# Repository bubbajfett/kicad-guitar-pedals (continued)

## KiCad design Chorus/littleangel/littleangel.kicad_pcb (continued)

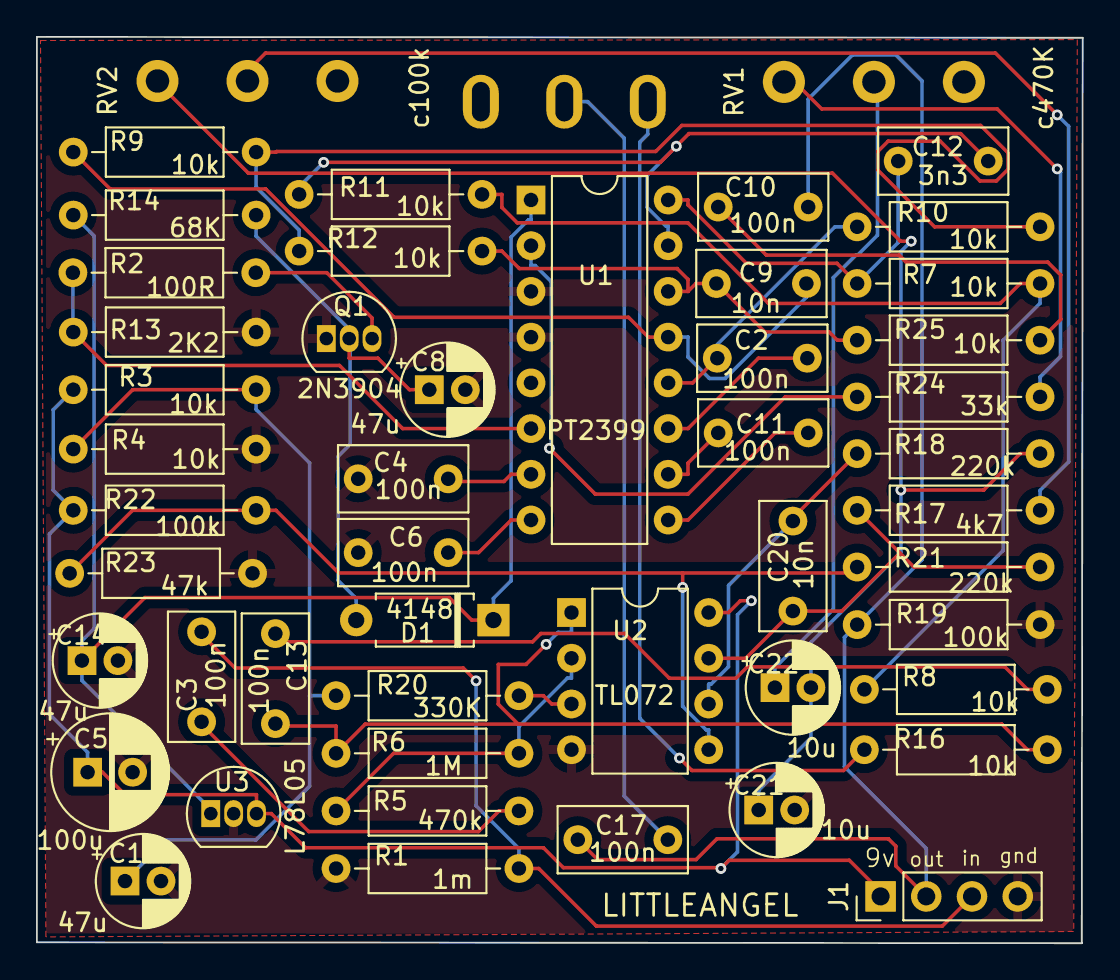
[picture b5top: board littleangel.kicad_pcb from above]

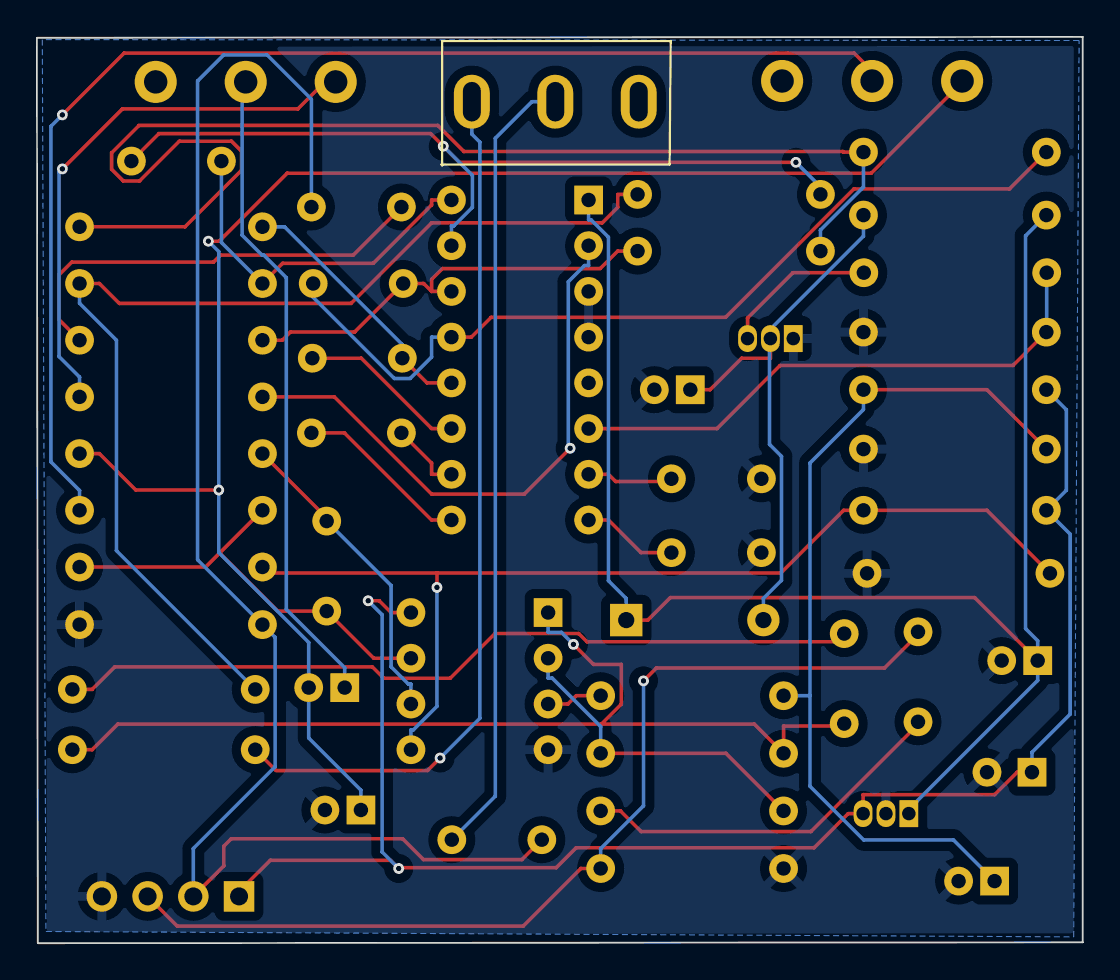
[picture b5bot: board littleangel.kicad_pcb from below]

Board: 2 copper layers, 58.1 x 50.3 mm, 50 parts (3 on the bottom side), 37 nets.

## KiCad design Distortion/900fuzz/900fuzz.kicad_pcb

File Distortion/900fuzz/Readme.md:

# 900 Fuzz

This is a clone of the 900 Fuzz by Fairfield Circuitry.

The first build had a "non-connected" base of Q4. I missed it, and
none of the kicad rules-checker caught it, or I ignored it.   Anyway,
the 2nd try I was more careful not to ignore any ERC errors.

This was based on the Pedalpcb NeinFuzz schematic, which does not specify the JFET.    Dirtboxlayouts shows J201

All trademarks belong to their respective owners.

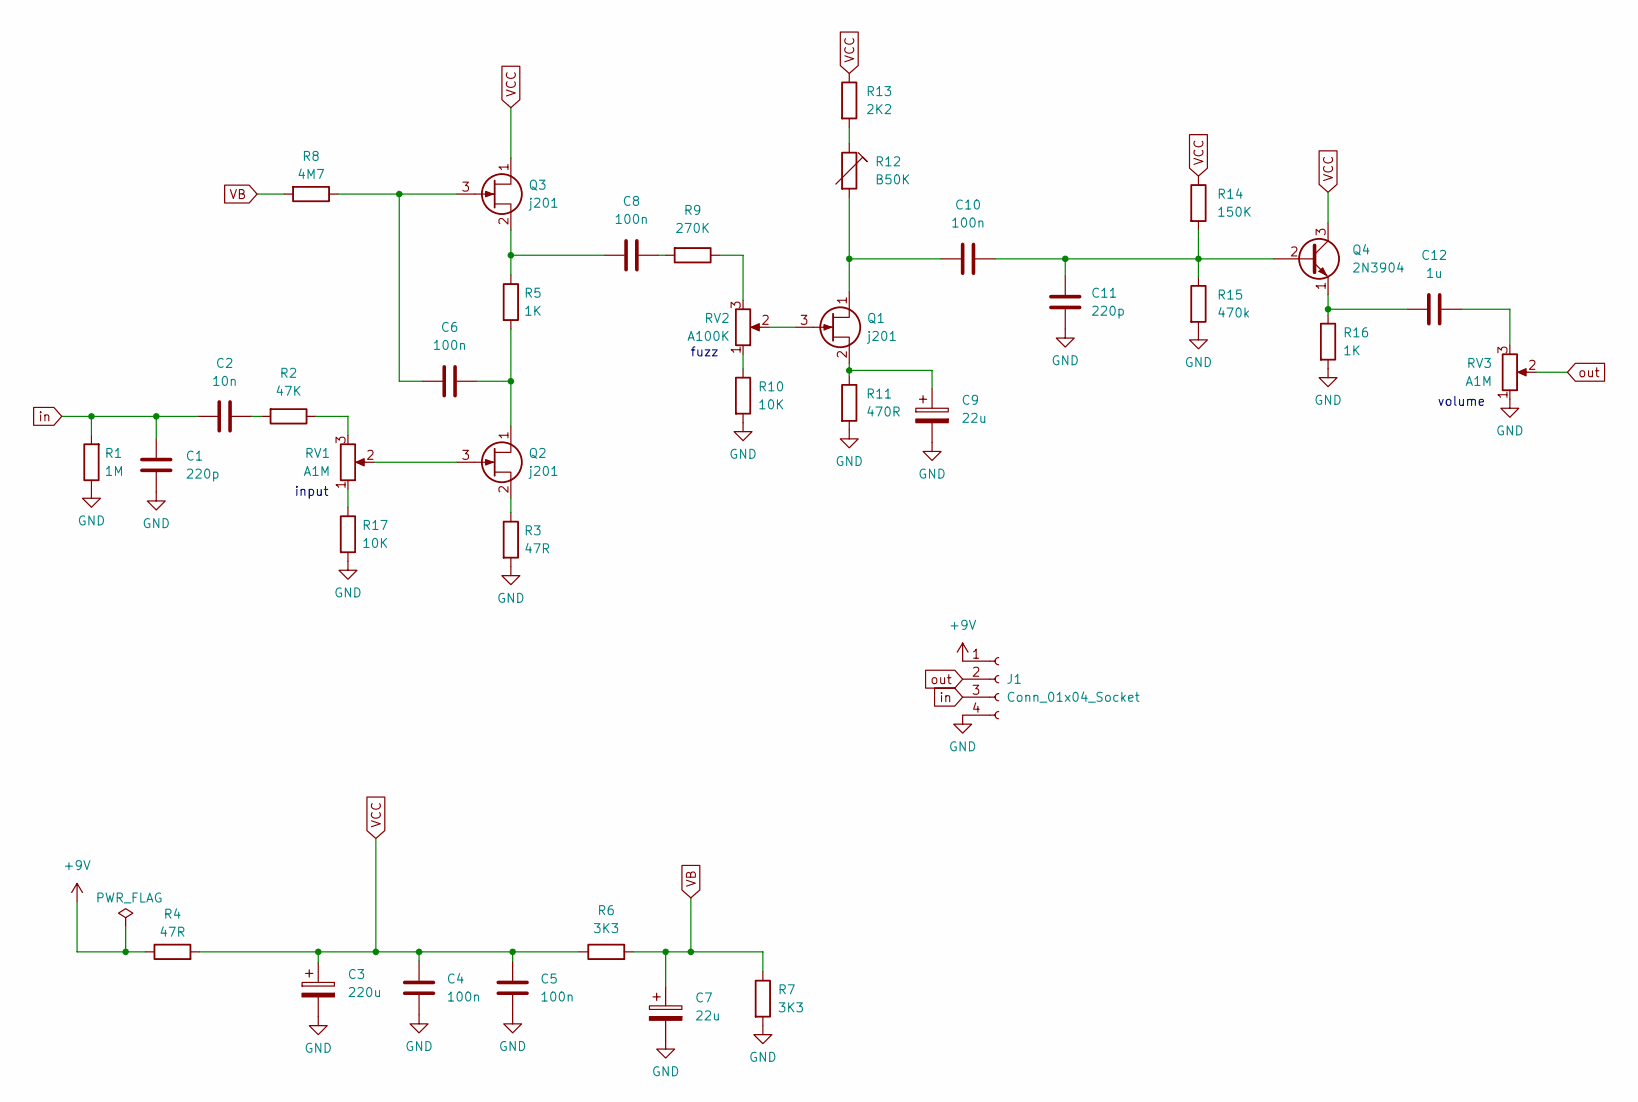
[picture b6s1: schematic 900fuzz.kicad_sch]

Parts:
C1, C11: 220p; C_Disc_D5.0mm_W2.5mm_P2.50mm
C2: 10n; C_Rect_L7.0mm_W2.5mm_P5.00mm
C3: 220u; CP_Radial_D6.3mm_P2.50mm
C4, C5, C6, C8, C10: 100n; C_Rect_L7.0mm_W2.5mm_P5.00mm
C7, C9: 22u; CP_Radial_D5.0mm_P2.00mm
C12: 1u; C_Rect_L7.0mm_W2.5mm_P5.00mm
J1: Conn_01x04_Socket; PinHeader_1x04_P2.54mm_Vertical
Q1, Q2, Q3: j201; TO92-SMD
Q4: 2N3904; TO-92_Inline_Wide
R1: 1M; R_Axial_DIN0207_L6.3mm_D2.5mm_P10.16mm_Horizontal
R2: 47K; R_Axial_DIN0207_L6.3mm_D2.5mm_P10.16mm_Horizontal
R3, R4: 47R; R_Axial_DIN0207_L6.3mm_D2.5mm_P10.16mm_Horizontal
R5, R16: 1K; R_Axial_DIN0207_L6.3mm_D2.5mm_P10.16mm_Horizontal
R6, R7: 3K3; R_Axial_DIN0207_L6.3mm_D2.5mm_P10.16mm_Horizontal
R8: 4M7; R_Axial_DIN0207_L6.3mm_D2.5mm_P10.16mm_Horizontal
R9: 270K; R_Axial_DIN0207_L6.3mm_D2.5mm_P10.16mm_Horizontal
R10, R17: 10K; R_Axial_DIN0207_L6.3mm_D2.5mm_P10.16mm_Horizontal
R11: 470R; R_Axial_DIN0207_L6.3mm_D2.5mm_P10.16mm_Horizontal
R12: B50K; Potentiometer_Runtron_RM-065_Vertical
R13: 2K2; R_Axial_DIN0207_L6.3mm_D2.5mm_P10.16mm_Horizontal
R14: 150K; R_Axial_DIN0207_L6.3mm_D2.5mm_P10.16mm_Horizontal
R15: 470k; R_Axial_DIN0207_L6.3mm_D2.5mm_P10.16mm_Horizontal
RV1, RV3: A1M; Pot_Underside
RV2: A100K; Pot_Underside

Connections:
+9V: J1.1, R4.1
GND: C1.2, C3.2, C4.1, C5.1, C7.2, C9.2, C11.1, J1.4, R1.1, R3.2, R7.2, R10.2, R11.2, R15.2, R16.2, R17.2, RV3.1
unnamed: C2.2, R2.2
unnamed: C8.2, R9.2
unnamed: C12.2, RV3.3
unnamed: C10.1, Q1.1 (D), R12.2
unnamed: Q1.3 (G), RV2.2
unnamed: C9.1, Q1.2 (S), R11.1
unnamed: C6.2, Q2.1 (D), R5.2
unnamed: Q2.3 (G), RV1.2
unnamed: Q2.2 (S), R3.1
unnamed: C6.1, Q3.3 (G), R8.1
unnamed: C8.1, Q3.2 (S), R5.1
unnamed: C10.2, C11.2, Q4.2 (B), R14.2, R15.1
unnamed: C12.1, Q4.1 (E), R16.1
unnamed: R2.1, RV1.3
unnamed: R9.1, RV2.3
unnamed: R10.1, RV2.1
unnamed: R12.1, R13.2
unnamed: R17.1, RV1.1
VB: C7.1, R6.2, R7.1, R8.2
VCC: C3.1, C4.2, C5.2, Q3.1 (D), Q4.3 (C), R4.2, R6.1, R13.1, R14.1
in: C1.1, C2.1, J1.3, R1.2
out: J1.2, RV3.2

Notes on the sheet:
volume
fuzz
input

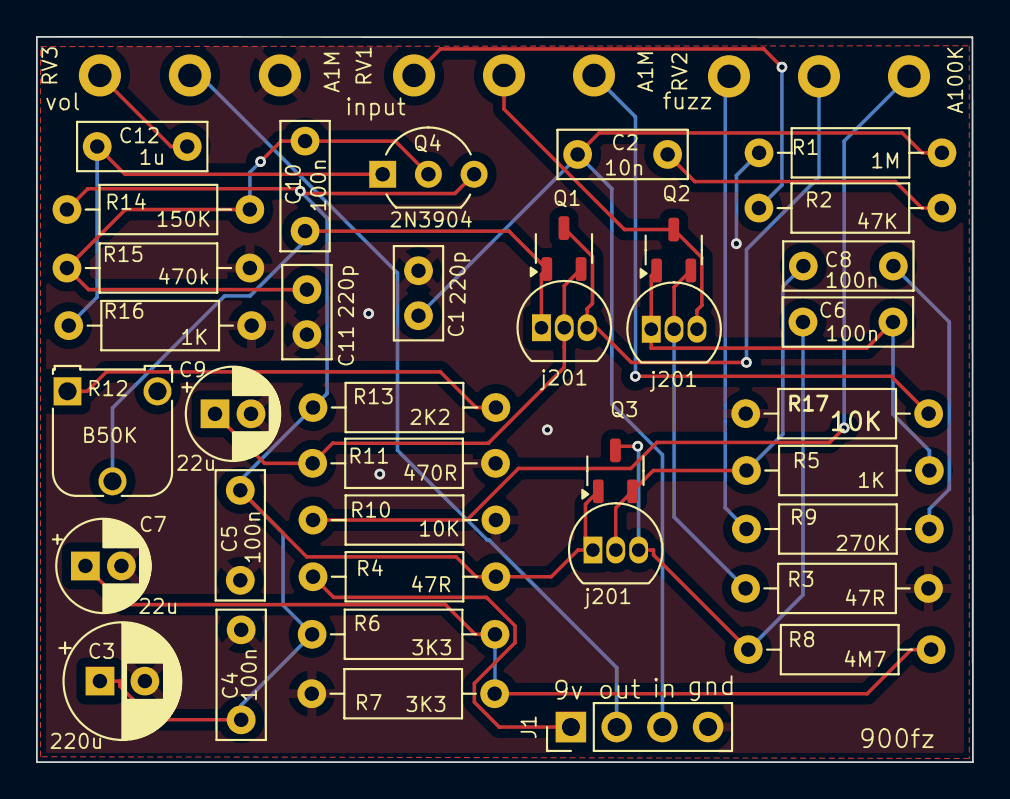
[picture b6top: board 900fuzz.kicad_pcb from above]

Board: 2 copper layers, 52.0 x 40.3 mm, 37 parts (0 on the bottom side), 24 nets.

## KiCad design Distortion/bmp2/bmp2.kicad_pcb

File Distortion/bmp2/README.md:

Big Muff Pi 2 clone 

This is based on a (modified?) Big Muff Op-amp version, that is the "modern
op-amp version of the EHX big muff pi".    

It is quite a bit more aggressive than the older, discreet transistor
BMP versions I've tried.

This is  verified.    At high sustain, it does motorboat a little in the build
I have.

Requires KICAD 7

All trademarks are owned by their respective owners.

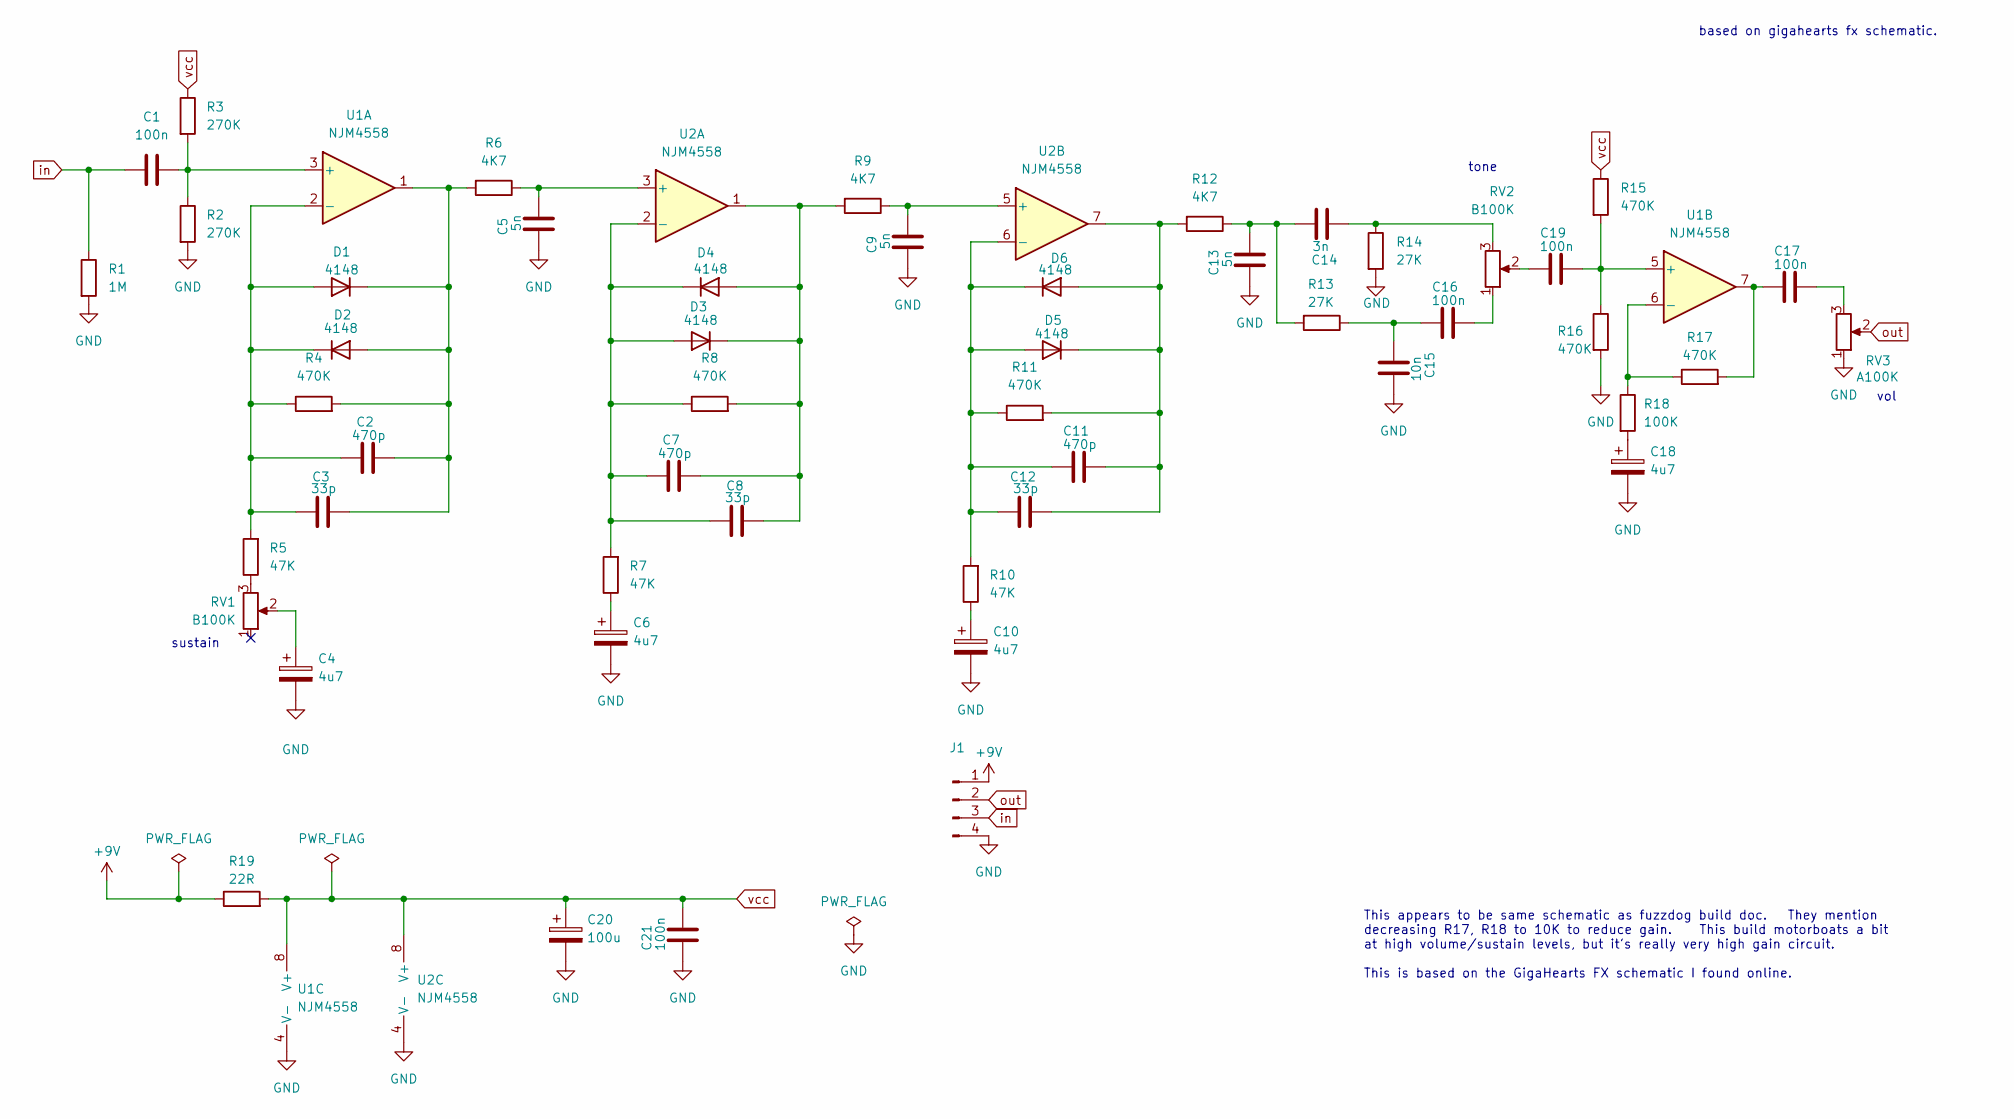
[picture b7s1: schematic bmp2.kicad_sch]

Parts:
C1, C16, C17, C19, C21: 100n; C_Rect_L7.0mm_W2.5mm_P5.00mm
C2, C7, C11: 470p; C_Disc_D5.0mm_W2.5mm_P2.50mm
C3, C8, C12: 33p; C_Disc_D5.0mm_W2.5mm_P2.50mm
C4, C6, C10, C18: 4u7; CP_Radial_D5.0mm_P2.00mm
C5, C9, C13: 5n; C_Rect_L7.0mm_W2.5mm_P5.00mm
C14: 3n; C_Rect_L7.0mm_W2.5mm_P5.00mm
C15: 10n; C_Rect_L7.0mm_W2.5mm_P5.00mm
C20: 100u; CP_Radial_D8.0mm_P2.50mm
D1, D2, D3, D4, D5, D6: 4148; D_DO-35_SOD27_P7.62mm_Horizontal
J1: Conn_01x04_Pin; PinHeader_1x04_P2.54mm_Vertical
R1: 1M; R_Axial_DIN0207_L6.3mm_D2.5mm_P10.16mm_Horizontal
R2, R3: 270K; R_Axial_DIN0207_L6.3mm_D2.5mm_P10.16mm_Horizontal
R4, R8, R11, R15, R16, R17: 470K; R_Axial_DIN0207_L6.3mm_D2.5mm_P10.16mm_Horizontal
R5, R7, R10: 47K; R_Axial_DIN0207_L6.3mm_D2.5mm_P10.16mm_Horizontal
R6, R9, R12: 4K7; R_Axial_DIN0207_L6.3mm_D2.5mm_P10.16mm_Horizontal
R13, R14: 27K; R_Axial_DIN0207_L6.3mm_D2.5mm_P10.16mm_Horizontal
R18: 100K; R_Axial_DIN0207_L6.3mm_D2.5mm_P10.16mm_Horizontal
R19: 22R; R_Axial_DIN0207_L6.3mm_D2.5mm_P10.16mm_Horizontal
RV1, RV2: B100K; Pot_Underside
RV3: A100K; Pot_Underside
U1, U2: NJM4558; DIP-8_W7.62mm

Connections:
+9V: J1.1, R19.1
GND: C4.2, C5.1, C6.2, C9.1, C10.2, C13.1, C15.2, C18.2, C20.2, C21.1, J1.4, R1.2, R2.2, R14.2, R16.2, RV3.1, U1.4 (V-), U2.4 (V-)
unnamed: C4.1, RV1.2
unnamed: C6.1, R7.1
unnamed: C10.1, R10.1
unnamed: C13.2, C14.2, R12.1, R13.2
unnamed: C14.1, R14.1, RV2.3
unnamed: C15.1, C16.1, R13.1
unnamed: C16.2, RV2.1
unnamed: C17.1, R17.2, U1.7
unnamed: C17.2, RV3.3
unnamed: C18.1, R18.2
unnamed: C19.1, RV2.2
unnamed: C2.1, C3.1, D1.2 (A), D2.1 (K), R4.1, R5.2, U1.2 (-)
unnamed: C2.2, C3.2, D1.1 (K), D2.2 (A), R4.2, R6.2, U1.1
unnamed: C7.1, C8.1, D3.2 (A), D4.1 (K), R7.2, R8.1, U2.2 (-)
unnamed: C7.2, C8.2, D3.1 (K), D4.2 (A), R8.2, R9.2, U2.1
unnamed: C11.1, C12.1, D5.2 (A), D6.1 (K), R10.2, R11.1, U2.6 (-)
unnamed: C11.2, C12.2, D5.1 (K), D6.2 (A), R11.2, R12.2, U2.7
unnamed: R5.1, RV1.3
unnamed: C1.2, R2.1, R3.2, U1.3 (+)
unnamed: C19.2, R15.2, R16.1, U1.5 (+)
unnamed: R17.1, R18.1, U1.6 (-)
unnamed: C5.2, R6.1, U2.3 (+)
unnamed: C9.2, R9.1, U2.5 (+)
in: C1.1, J1.3, R1.1
out: J1.2, RV3.2
vcc: C20.1, C21.2, R3.1, R15.1, R19.2, U1.8 (V+), U2.8 (V+)

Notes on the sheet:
vol
tone
sustain
This appears to be same schematic as fuzzdog build doc. They mention decreasing R17, R18 to 10K to reduce gain. This build motorboats a bit at high volume/sustain levels, but it's really very high gain circuit. This is based on the GigaHearts FX schematic I found online.
based on gigahearts fx schematic.

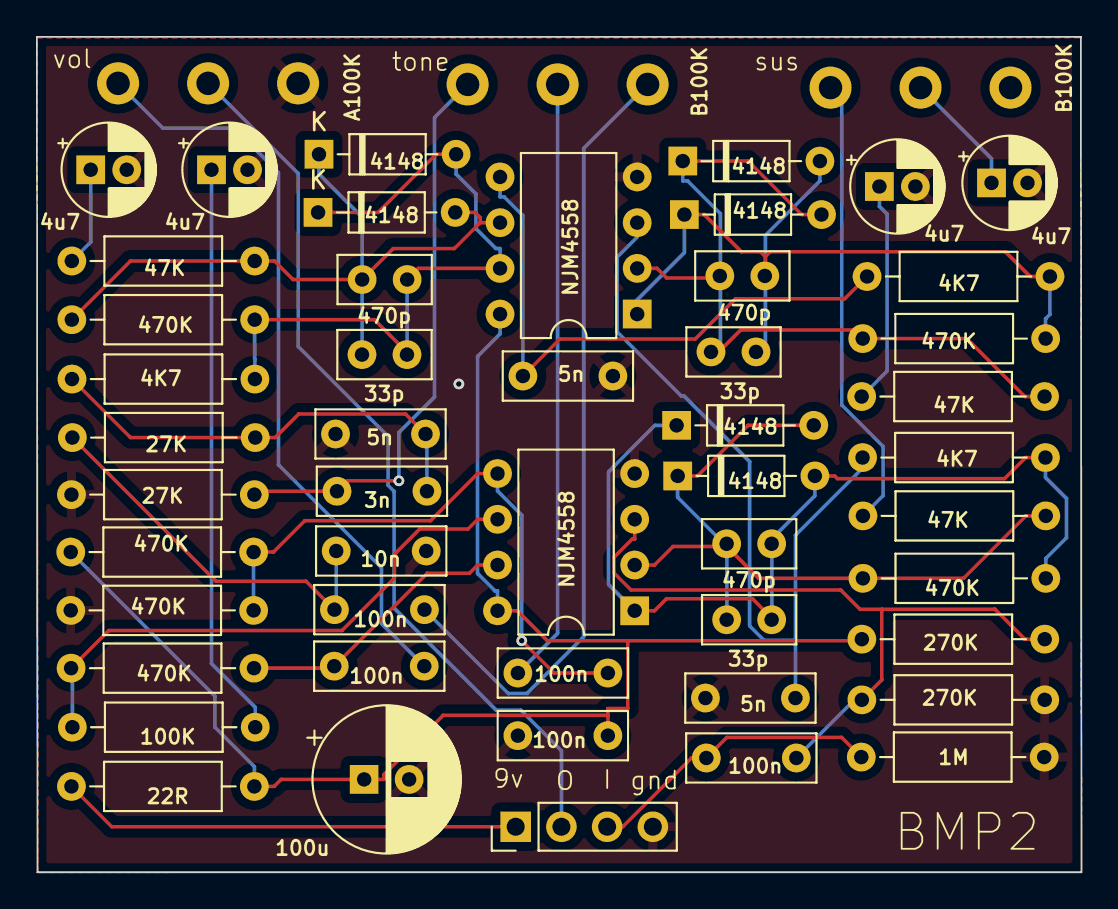
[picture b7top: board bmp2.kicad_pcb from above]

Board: 2 copper layers, 58.0 x 46.4 mm, 52 parts (0 on the bottom side), 28 nets.

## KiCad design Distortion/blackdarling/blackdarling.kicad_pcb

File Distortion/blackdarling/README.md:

MrBlack Darling Fuzz clone

Saw this on DirtboxLayouts, and decided to try it.    Was originally
looking for the Soulkitchen heavy darling fuzz, and could not find a
schematic for it.    Decided this might be a nice replacement.

Nice fuzz.   

Requires KICAD 7

All trademarks are owned by their respective owners.

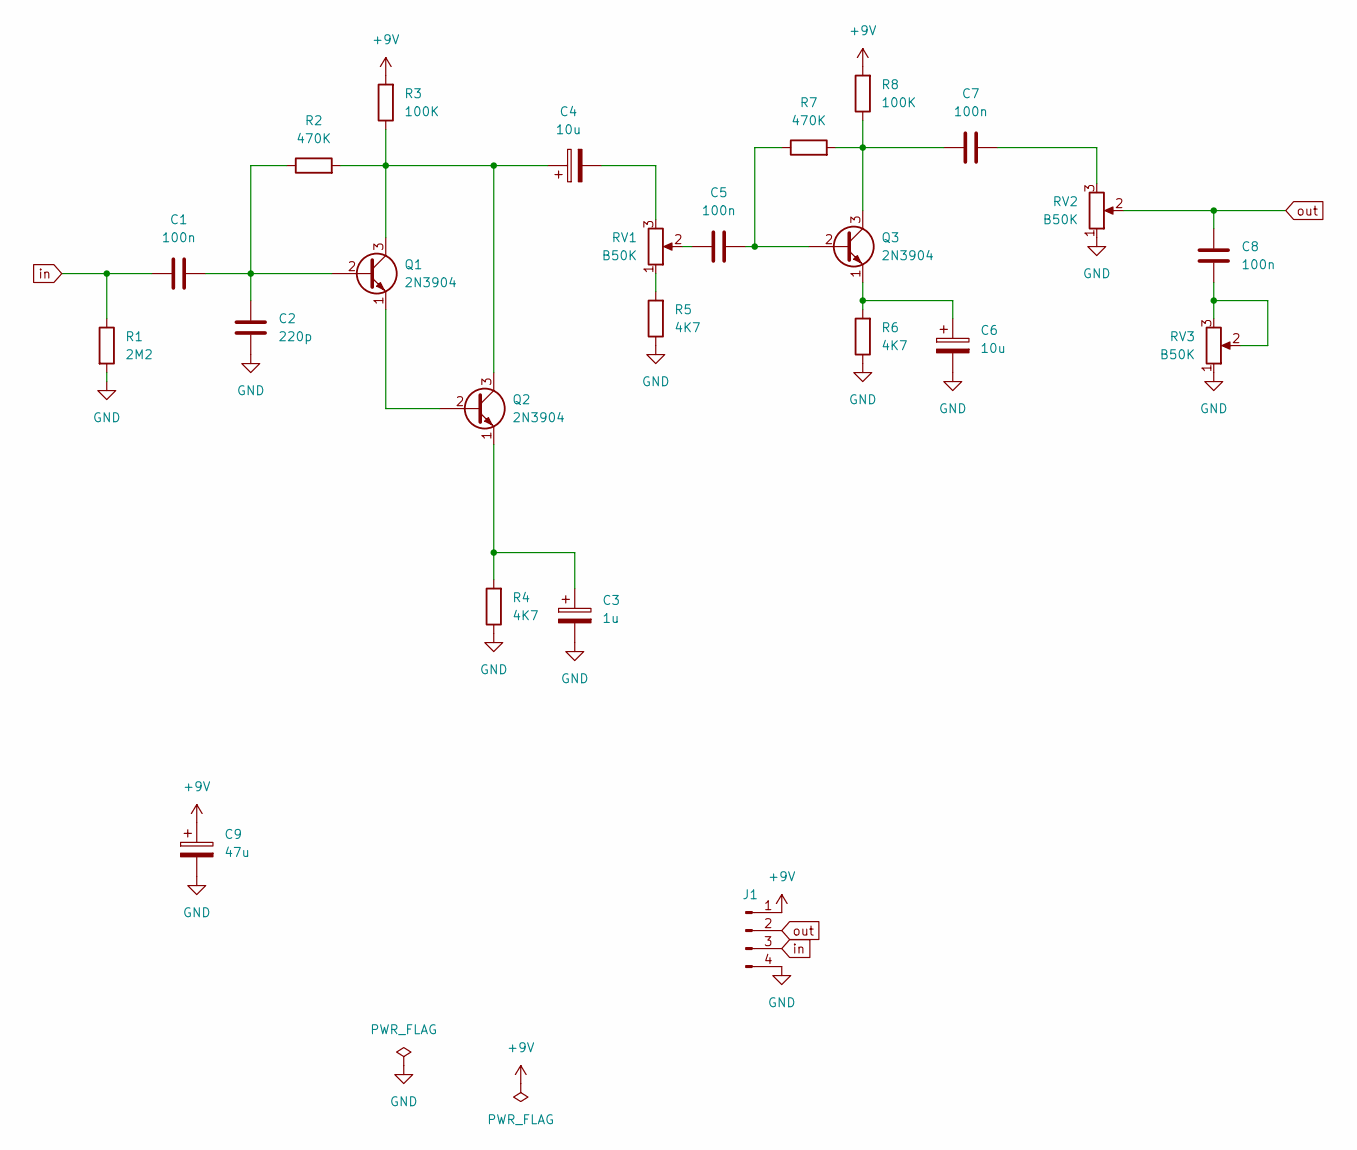
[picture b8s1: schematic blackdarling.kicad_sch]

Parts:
C1, C5, C7, C8: 100n; C_Rect_L7.0mm_W2.5mm_P5.00mm
C2: 220p; C_Disc_D3.8mm_W2.6mm_P2.50mm
C3: 1u; CP_Radial_D5.0mm_P2.00mm
C4, C6: 10u; CP_Radial_D5.0mm_P2.00mm
C9: 47u; CP_Radial_D6.3mm_P2.50mm
J1: Conn_01x04_Pin; PinHeader_1x04_P2.54mm_Vertical
Q1, Q2, Q3: 2N3904; TO-92_Inline
R1: 2M2; R_Axial_DIN0207_L6.3mm_D2.5mm_P10.16mm_Horizontal
R2, R7: 470K; R_Axial_DIN0207_L6.3mm_D2.5mm_P10.16mm_Horizontal
R3, R8: 100K; R_Axial_DIN0207_L6.3mm_D2.5mm_P10.16mm_Horizontal
R4, R5, R6: 4K7; R_Axial_DIN0207_L6.3mm_D2.5mm_P10.16mm_Horizontal
RV1, RV2, RV3: B50K; Pot_Underside

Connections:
+9V: C9.1, J1.1, R3.2, R8.2
GND: C2.1, C3.2, C6.2, C9.2, J1.4, R1.2, R4.1, R5.1, R6.1, RV2.1, RV3.1
unnamed: C4.2, RV1.3
unnamed: C5.1, RV1.2
unnamed: C7.1, RV2.3
unnamed: C8.2, RV3.2, RV3.3
unnamed: C1.2, C2.2, Q1.2 (B), R2.1
unnamed: C4.1, Q1.3 (C), Q2.3 (C), R2.2, R3.1
unnamed: Q1.1 (E), Q2.2 (B)
unnamed: C3.1, Q2.1 (E), R4.2
unnamed: C5.2, Q3.2 (B), R7.1
unnamed: C7.2, Q3.3 (C), R7.2, R8.1
unnamed: C6.1, Q3.1 (E), R6.2
unnamed: R5.2, RV1.1
in: C1.1, J1.3, R1.1
out: C8.1, J1.2, RV2.2

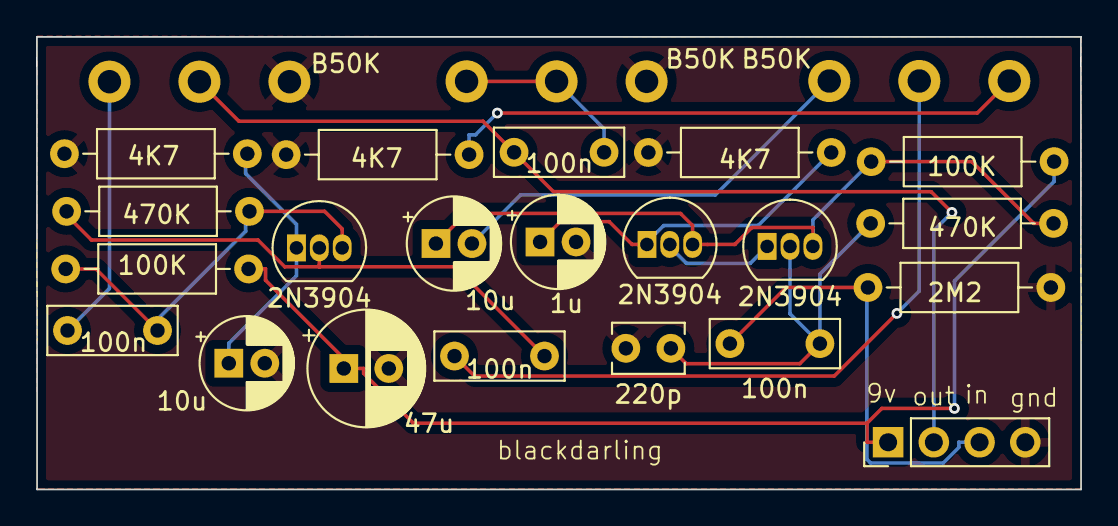
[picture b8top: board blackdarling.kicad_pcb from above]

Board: 2 copper layers, 58.0 x 25.1 mm, 24 parts (0 on the bottom side), 16 nets.

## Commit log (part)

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2026-02-08 Moving repos into a single repo
2026-02-08 added two additional pedals -- whitefuzz and harmonicpercolator
2026-02-22 Added timmy drive
2026-02-22 Added timmy
2026-02-27 added tweed57 overdrive
    updated layout of the chargepump pcb
2026-03-01 added the badmonkey pedal
2026-03-04 added fatdrive
2026-03-09 re-generated the Fatdrive and badmonkey boards, as they were just a hair too large for the enclosures I am using.
    x
2026-03-16 Added Overdrive-07-ecstacy
2026-03-16 Added Readme.md
2026-03-16 added acapulco gold
2026-03-16 removed zip file
2026-04-02 reorg
2026-04-02 missing files
2026-04-02 cleanup
2026-04-15 mutron prl
2026-04-25 fix to badmonkey -- pedal works but the schematic this was based on does not seem right. There's a voltage offset on the input when engaged, and this messes with it in the pedal chain.
2026-05-03 added 6 band eq, and fuzzface distortion
2026-05-03 added deep_blue_delay
2026-05-16 added repo listing
2026-05-23 updated readme, comments on fatdrive schematic
2026-05-25 added triple wreck
2026-05-26 added triple_wreck
2026-05-27 added overdrive/ocd
2026-06-08 added engineers thumb, ramshead-bmp
2026-06-09 added top-jacks and stomp-3pdt
2026-06-25 added ejfuzzface
2026-06-27 replaced whiefuzz, and modified ejfuzzface
2026-06-28 top jacks gerbers.
